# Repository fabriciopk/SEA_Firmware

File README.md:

# SEA_Firmware
Firmware for series elastic actuator, this board contains a stm32f103 microcontroller

#Installation(Upload using arduino IDE)

- Download arduino [IDE](https://www.arduino.cc/en/Main/Software)
- Download zip file containing the STM32 files from [here](https://github.com/fabriciopk/Arduino_STM32/archive/master.zip)
- Unzip in arduino hardware folder (arduino-1.6.xx/hardware/) and rename to Arduino_STM32
- Run the arduino IDE, and on the Tools menu, select the Boards manager (Tools > Boards > Boards Manager), and install the Arduino Zero(Arduino SAMD boards 32 bits cortex M3) from the list of available boards. You must do this step, it installs the arm-none-eabi-g++ toolchain!
- Copy AS5048A and DynamixelProtocol from [lib](https://github.com/fabriciopk/SEA_Firmware/tree/master/lib) folder to (arduino-1.6.xx/libraries/)
- Change the line #define BOARD_HAVE_SERIALUSB 0 in the file arduino-1.6.xx/hardware/STM32F1/cores/maple/boards.h 

#Setup Arduino IDE and board upload pins
- Board:STM32F103C Generic
- Variant:STM32F103C8
- Upload method: Stlink
- Open [src/src.ino](https://github.com/fabriciopk/SEA_Firmware/blob/master/src/src.ino)
- Pins for SWD(stlink v.2) setup:

NOTE: top-side of board.
#Board settings
```c++
#define SEA_ID 105 //define the board id in rs485 network
#define INVERTED
...
#define SEA_RECT //Type of the board, coment if is the rounded board
...
```
#Testing(linux)

Plug usb2Dinamyxel, power on the board.
```bash
cd test_board
make
./dynamixel_test ID_board
```

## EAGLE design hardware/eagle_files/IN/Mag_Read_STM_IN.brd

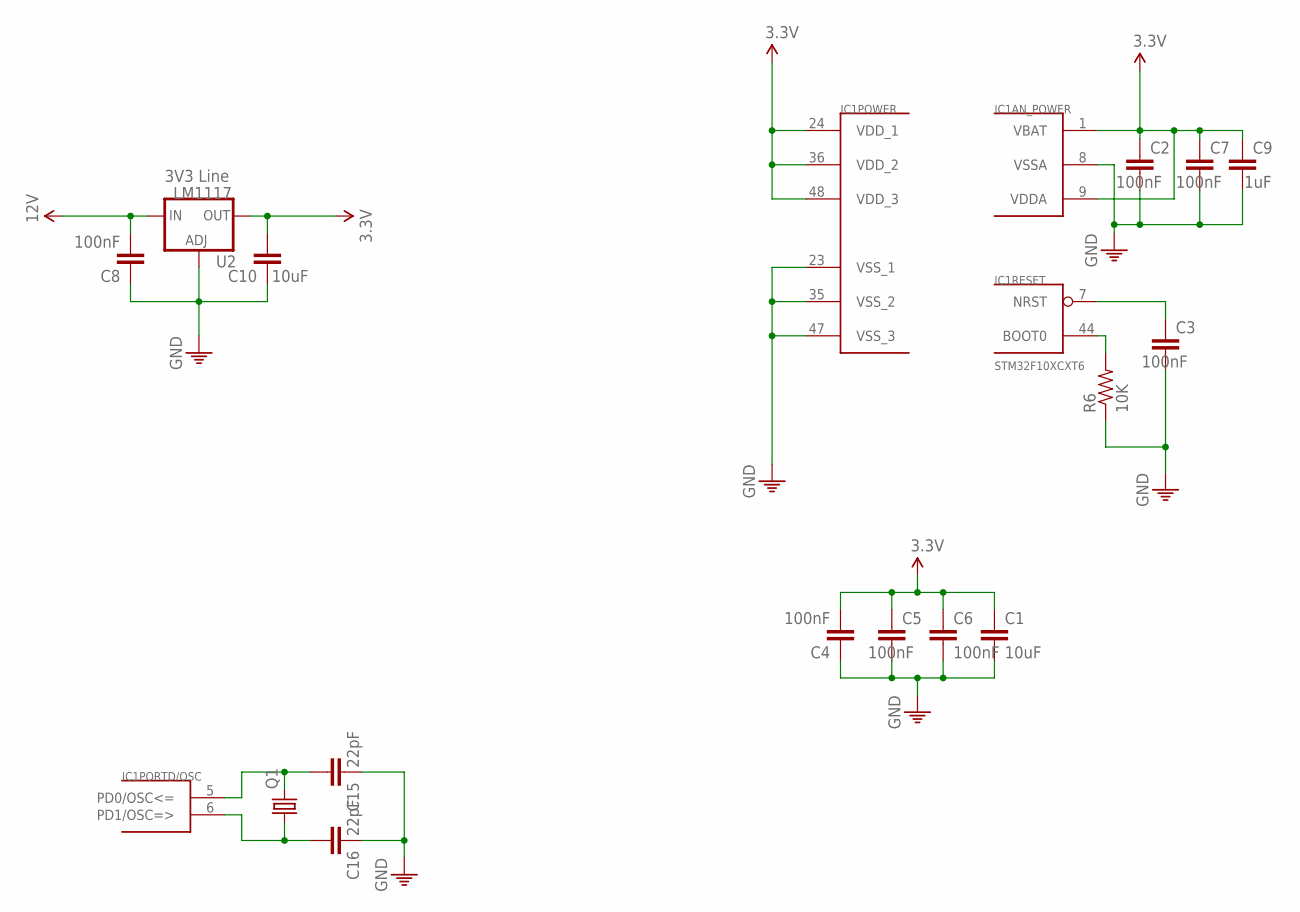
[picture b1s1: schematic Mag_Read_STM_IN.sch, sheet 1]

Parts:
C1, C10: 10uF; C0603
C2, C3, C4, C5, C6, C7, C8: 100nF; C0603
C9: 1uF; C0603
C15, C16: 22pF; C0603
IC1: STM32F10XCXT6; TQFP48
Q1: CRYSTALCTS406; CTS406
R6: 10K; 0603-RES
U2: LM1117; SOT223

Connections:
3.3V: C1.1, C2.1, C4.2, C5.1, C6.1, C7.1, C9.1, C10.2, IC1.1 (VBAT), IC1.9 (VDDA), IC1.24 (VDD_1), IC1.36 (VDD_2), IC1.48 (VDD_3), U2.2 (OUT), U2.4 (OUT); also elsewhere on the board
12V: C8.2, U2.3 (IN); also elsewhere on the board
GND: C1.2, C2.2, C3.2, C4.1, C5.2, C6.2, C7.2, C8.1, C9.2, C10.1, C15.1, C16.1, IC1.8 (VSSA), IC1.23 (VSS_1), IC1.35 (VSS_2), IC1.47 (VSS_3), R6.1, U2.1 (ADJ); also elsewhere on the board
unnamed: C15.2, IC1.5 (PD0/OSC<=), Q1.3 (2)
unnamed: C16.2, IC1.6 (PD1/OSC=>), Q1.1
unnamed: IC1.44 (BOOT0), R6.2
NRST: C3.1, IC1.7 (NRST); also elsewhere on the board

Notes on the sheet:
3V3 Line

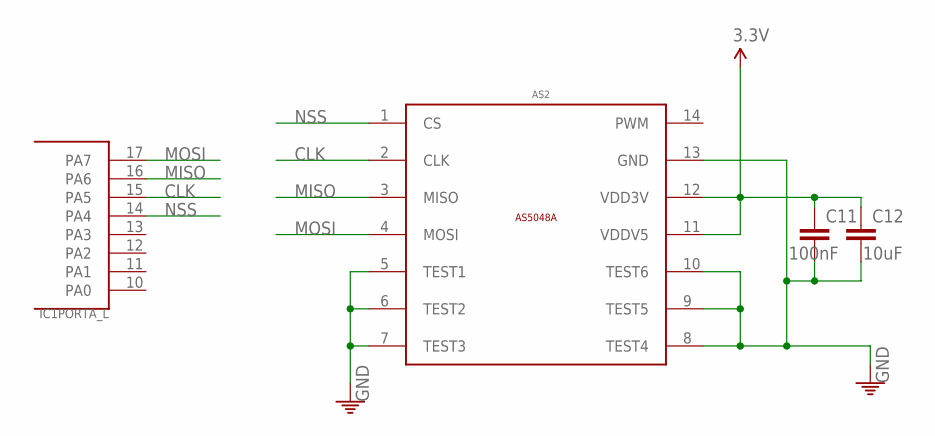
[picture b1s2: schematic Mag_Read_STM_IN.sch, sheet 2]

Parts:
AS2: AS5048A_MAGNETIC_ROTARY_ENCODERTSSOP14; AS5048A_14-TSSOP
C11: 100nF; C0603
C12: 10uF; C0603
IC1: STM32F10XCXT6; TQFP48

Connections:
3.3V: AS2.11 (VDDV5), AS2.12 (VDD3V), C11.1, C12.1; also elsewhere on the board
CLK: AS2.2 (CLK), IC1.15 (PA5)
GND: AS2.5 (TEST1), AS2.6 (TEST2), AS2.7 (TEST3), AS2.8 (TEST4), AS2.9 (TEST5), AS2.10 (TEST6), AS2.13 (GND), C11.2, C12.2; also elsewhere on the board
MISO: AS2.3 (MISO), IC1.16 (PA6)
MOSI: AS2.4 (MOSI), IC1.17 (PA7)
NSS: AS2.1 (CS), IC1.14 (PA4)

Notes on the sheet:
MISO
MOSI
NSS
CLK

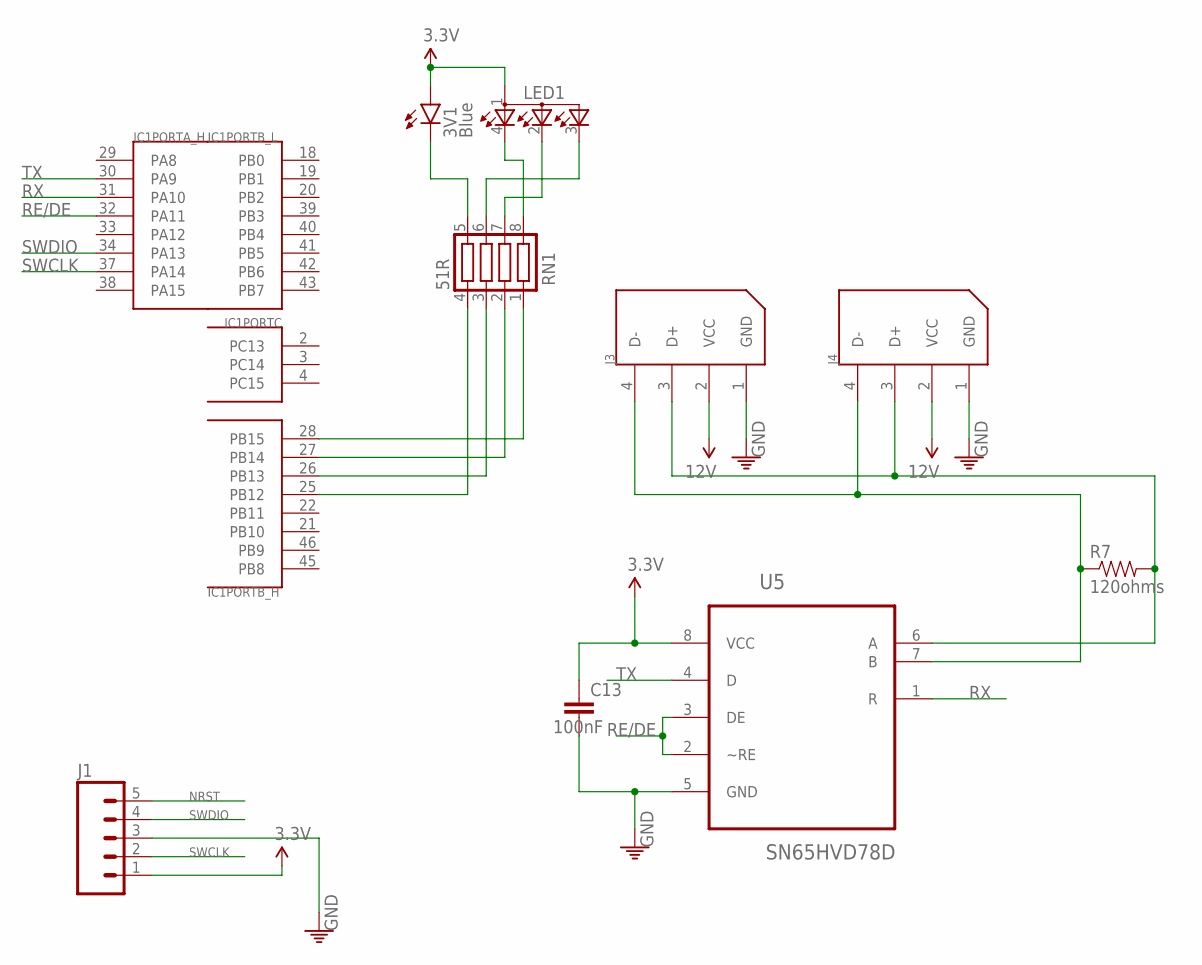
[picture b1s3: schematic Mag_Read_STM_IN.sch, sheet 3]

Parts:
3V1: Blue; LED-0603
C13: 100nF; C0603
IC1: STM32F10XCXT6; TQFP48
J1: M05PTH; 1X05
J3, J4: 22-03-5045; 5267-4
LED1: TOPLED-3; P-LCC-4-3
R7: 120ohms; 0603-RES
RN1: 51R; CAY10-XXXJ4
U5: SN65HVD78D; SOIC127P600X175-8N

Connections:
3.3V: 3V1.A, C13.1, J1.1, LED1.1 (A2), U5.8 (VCC); also elsewhere on the board
12V: J3.2 (VCC), J4.2 (VCC); also elsewhere on the board
D+: J3.3 (D+), J4.3 (D+), R7.2, U5.6 (A)
D-: J3.4 (D-), J4.4 (D-), R7.1, U5.7 (B)
GND: C13.2, J1.3, J3.1 (GND), J4.1 (GND), U5.5 (GND); also elsewhere on the board
unnamed: 3V1.C, RN1.5
unnamed: IC1.28 (PB15), RN1.1
unnamed: IC1.27 (PB14), RN1.2
unnamed: IC1.26 (PB13), RN1.3
unnamed: LED1.3 (CGREEN), RN1.6
unnamed: LED1.2 (CBLUE), RN1.7
unnamed: LED1.4 (CRED), RN1.8
unnamed: IC1.25 (PB12), RN1.4
NRST: J1.5; also elsewhere on the board
RE/DE: IC1.32 (PA11), U5.2 (~RE), U5.3 (DE)
RX: IC1.31 (PA10), U5.1 (R)
SWCLK: IC1.37 (PA14), J1.2
SWDIO: IC1.34 (PA13), J1.4
TX: IC1.30 (PA9), U5.4 (D)

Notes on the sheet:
RE/DE
SWCLK
SWDIO
NRST

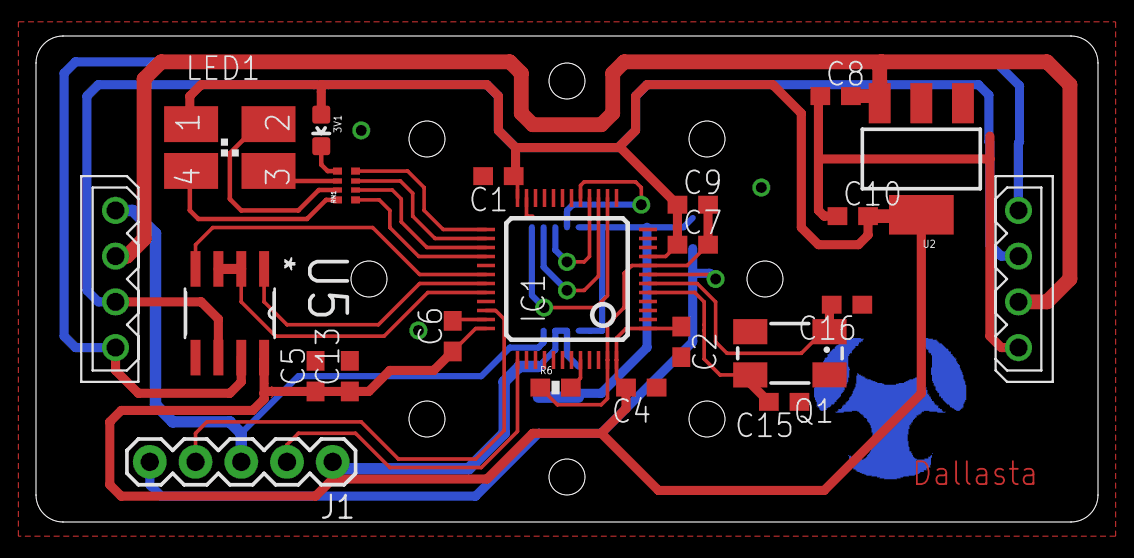
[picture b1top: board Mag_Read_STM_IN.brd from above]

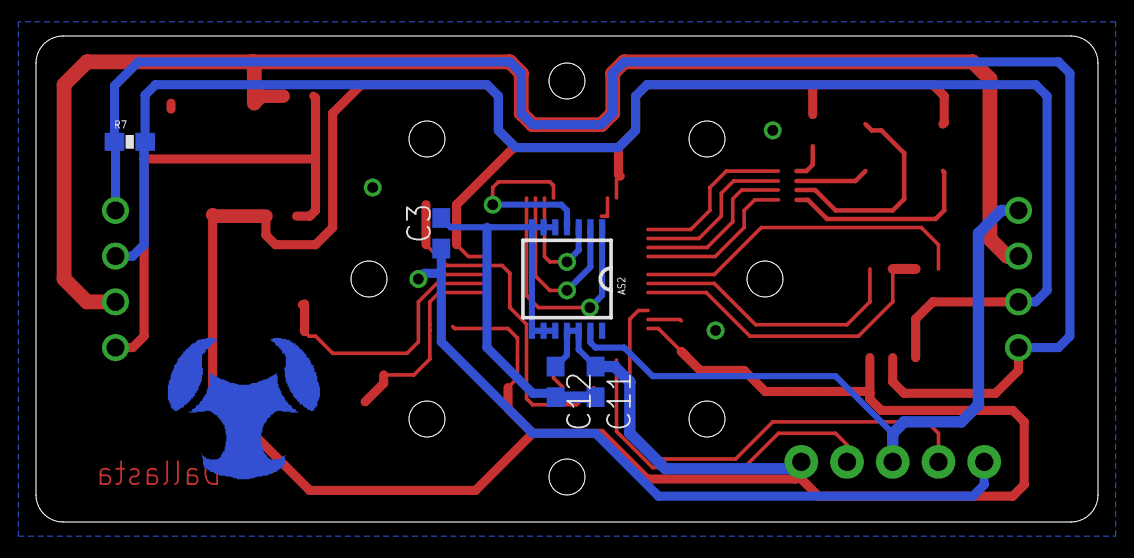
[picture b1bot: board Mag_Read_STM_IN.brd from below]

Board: 2 copper layers, 59.0 x 27.0 mm, 28 parts (5 on the bottom side), 26 nets.

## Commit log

2016-10-10 Add source code
2016-10-10 CI test
2016-10-10 Added dynamixel and magnetometer libraries
2016-10-10 Test CI
2016-10-10 New firmware for stm32f103c8
2016-10-11 Added new makefile for flash the device
2016-10-11 Add some files
2016-10-12 Add some notes
2016-10-13 Fix some bugs
2016-10-14 Fix pins definitions
2016-10-25 Added new functions
2016-10-27 Added serial as parameter to constructor DynamixelProtocol
2016-10-27 Passing Serial as parameter
2016-12-20 Rename main code
2016-12-20 Hardware setup
2016-12-20 update hardware pictures
2017-02-05 partlist
2017-02-05 src change

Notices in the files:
parts and their libraries:
SparkFun-LED: Licensing: Creative Commons ShareAlike 4.0 International - https://creativecommons.org/licenses/by-sa/4.0
